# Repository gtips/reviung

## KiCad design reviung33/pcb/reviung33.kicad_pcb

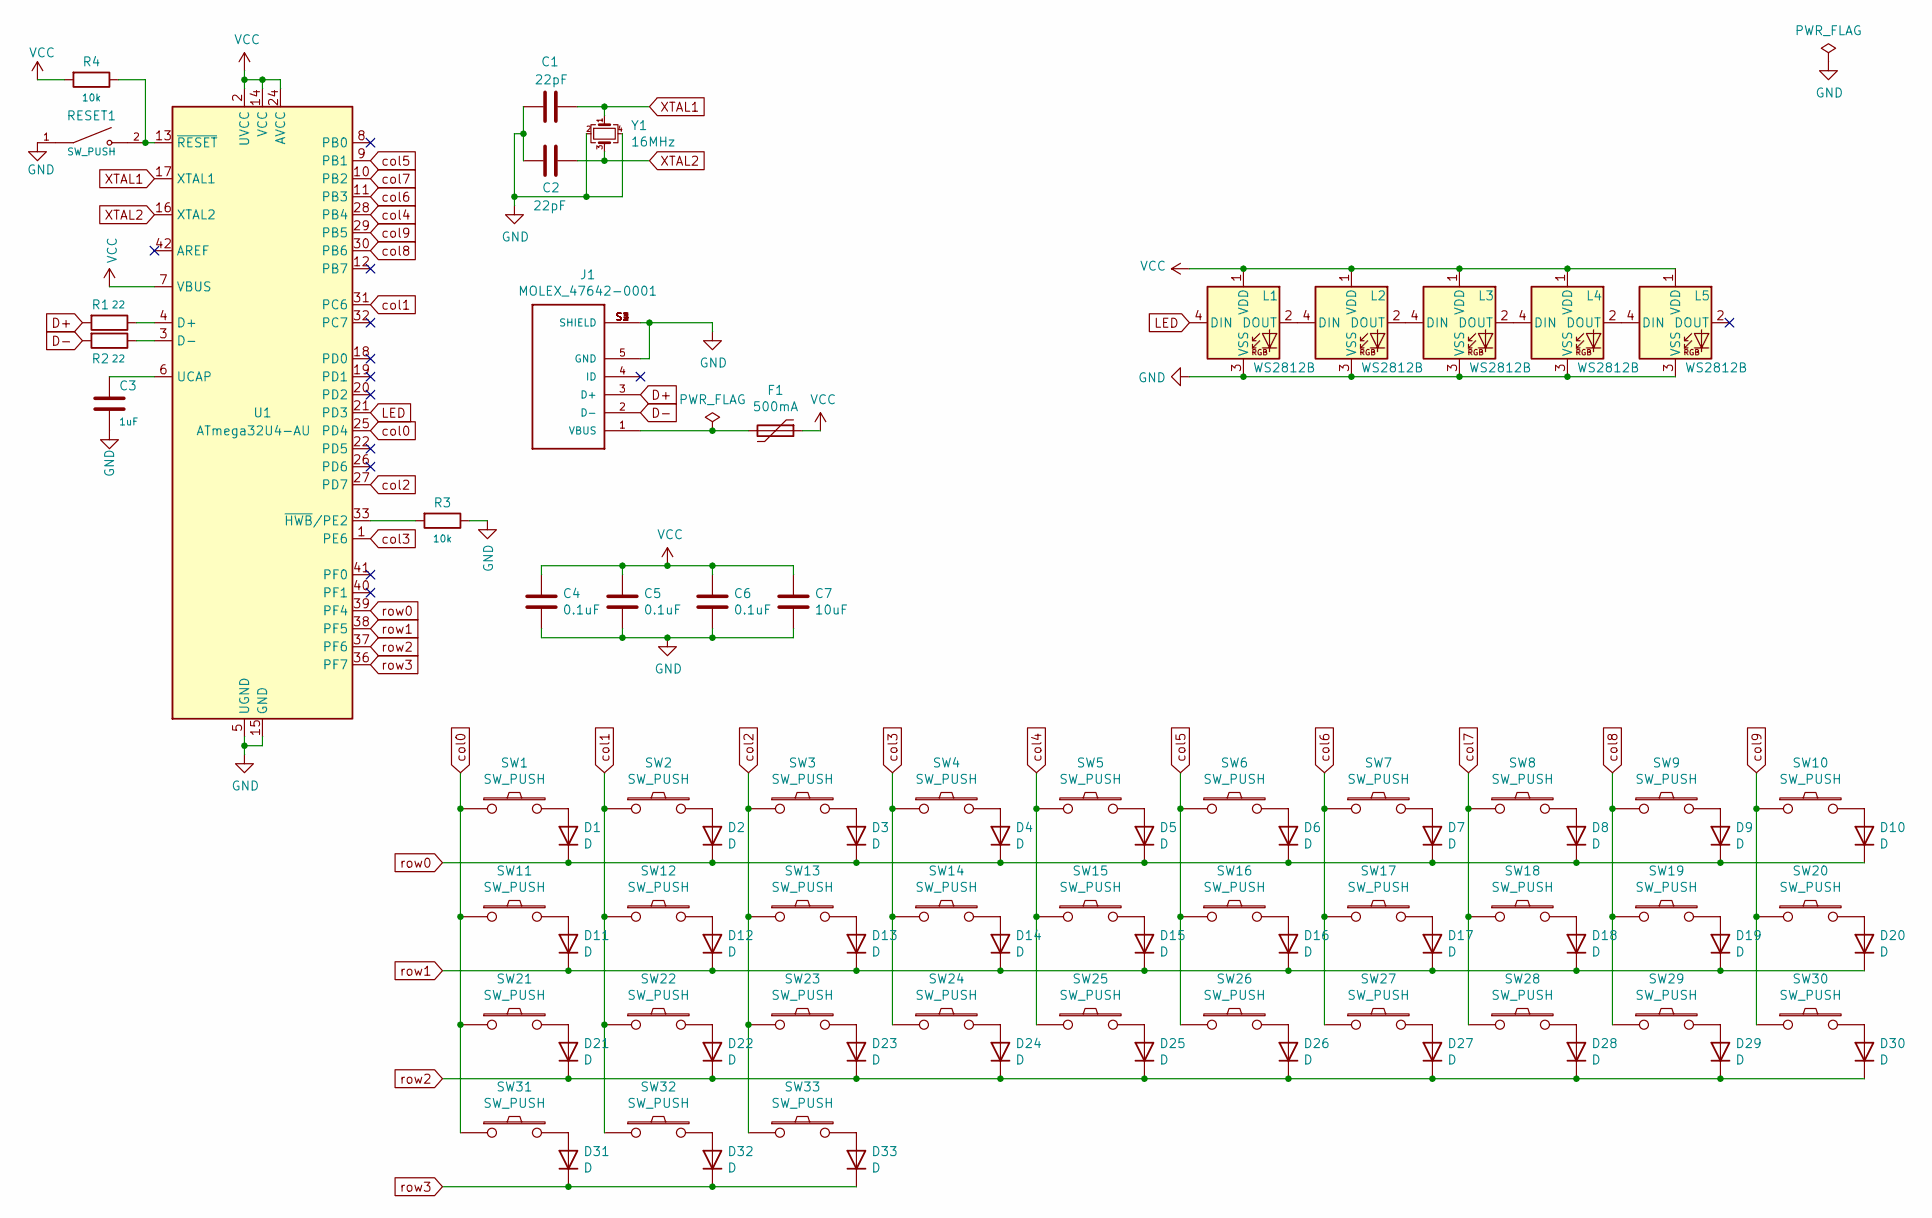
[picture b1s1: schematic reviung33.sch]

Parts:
C1, C2: 22pF; C_1206_3216Metric_Pad1.42x1.75mm_HandSolder
C3: 1uF; C_1206_3216Metric_Pad1.42x1.75mm_HandSolder
C4, C5, C6: 0.1uF; C_1206_3216Metric_Pad1.42x1.75mm_HandSolder
C7: 10uF; C_1206_3216Metric_Pad1.42x1.75mm_HandSolder
D1, D2, D3, D4, D5, D6, D7, D8, D9, D10, D11, D12, D13, D14, D15, D16, D17, D18, D19, D20, D21, D22, D23, D24, D25, D26, D27, D28, D29, D30, D31, D32, D33: D; D3_SMD_1side
F1: 500mA; Fuse_0805_2012Metric_Pad1.15x1.40mm_HandSolder
J1: MOLEX_47642-0001; MOLEX_47642-0001_HandSoldering_cuts
L1, L2, L3, L4, L5: WS2812B; LED_WS2812B_PLCC4_5.0x5.0mm_P3.2mm
R1, R2: 22; R_1206_3216Metric_Pad1.42x1.75mm_HandSolder
R3, R4: 10k; R_1206_3216Metric_Pad1.42x1.75mm_HandSolder
RESET1: SW_PUSH; SW_SPST_B3U-1000P
SW1, SW2, SW3, SW4, SW5, SW6, SW7, SW8, SW9, SW10, SW11, SW12, SW13, SW14, SW15, SW16, SW17, SW18, SW19, SW20, SW21, SW22, SW23, SW24, SW25, SW26, SW27, SW28, SW29, SW30, SW31, SW33: SW_PUSH; MXOnly-1U-Hotswap
SW32: SW_PUSH; MXOnly-6.25U-Hotswap-ReversedStabilizers
U1: ATmega32U4-AU; TQFP-44_10x10mm_P0.8mm
Y1: 16MHz; Crystal_SMD_3225-4Pin_3.2x2.5mm_HandSoldering

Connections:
D+: J1.3 (D+), R1.2
D-: J1.2 (D-), R2.2
GND: C1.1, C2.2, C3.2, C4.2, C5.2, C6.2, C7.2, J1.5 (GND), J1.S1 (SHIELD), J1.S2 (SHIELD), J1.S3 (SHIELD), J1.S4 (SHIELD), L1.3 (VSS), L2.3 (VSS), L3.3 (VSS), L4.3 (VSS), L5.3 (VSS), R3.1, RESET1.1, U1.5 (UGND), U1.15 (GND), U1.23 (GND), U1.35 (GND), U1.43 (GND), Y1.2, Y1.4; also elsewhere on the board
LED: L1.4 (DIN), U1.21 (PD3)
unnamed: C3.1, U1.6 (UCAP)
unnamed: D1.2 (A), SW1.2
unnamed: D2.2 (A), SW2.2
unnamed: D3.2 (A), SW3.2
unnamed: D4.2 (A), SW4.2
unnamed: D5.2 (A), SW5.2
unnamed: D6.2 (A), SW6.2
unnamed: D7.2 (A), SW7.2
unnamed: D8.2 (A), SW8.2
unnamed: D9.2 (A), SW9.2
unnamed: D10.2 (A), SW10.2
unnamed: D11.2 (A), SW11.2
unnamed: D12.2 (A), SW12.2
unnamed: D13.2 (A), SW13.2
unnamed: D14.2 (A), SW14.2
unnamed: D15.2 (A), SW15.2
unnamed: D16.2 (A), SW16.2
unnamed: D17.2 (A), SW17.2
unnamed: D18.2 (A), SW18.2
unnamed: D19.2 (A), SW19.2
unnamed: D20.2 (A), SW20.2
unnamed: D21.2 (A), SW21.2
unnamed: D22.2 (A), SW22.2
unnamed: D23.2 (A), SW23.2
unnamed: D24.2 (A), SW24.2
unnamed: D25.2 (A), SW25.2
unnamed: D26.2 (A), SW26.2
unnamed: D27.2 (A), SW27.2
unnamed: D28.2 (A), SW28.2
unnamed: D29.2 (A), SW29.2
unnamed: D30.2 (A), SW30.2
unnamed: D31.2 (A), SW31.2
unnamed: D32.2 (A), SW32.2
unnamed: D33.2 (A), SW33.2
unnamed: F1.2, J1.1 (VBUS)
unnamed: L1.2 (DOUT), L2.4 (DIN)
unnamed: L2.2 (DOUT), L3.4 (DIN)
unnamed: L3.2 (DOUT), L4.4 (DIN)
unnamed: L4.2 (DOUT), L5.4 (DIN)
unnamed: R1.1, U1.4 (D+)
unnamed: R2.1, U1.3 (D-)
unnamed: R3.2, U1.33 (~HWB~/PE2)
unnamed 46: R4.1, RESET1.2, U1.13 (~RESET); also elsewhere on the board
VCC: C4.1, C5.1, C6.1, C7.1, F1.1, L1.1 (VDD), L2.1 (VDD), L3.1 (VDD), L4.1 (VDD), L5.1 (VDD), R4.2, U1.2 (UVCC), U1.7 (VBUS), U1.14 (VCC), U1.24 (AVCC), U1.34 (VCC), U1.44 (AVCC)
XTAL1: C1.2, U1.17 (XTAL1), Y1.1
XTAL2: C2.1, U1.16 (XTAL2), Y1.3
col0: SW1.1, SW11.1, SW21.1, SW31.1, U1.25 (PD4)
col1: SW2.1, SW12.1, SW22.1, SW32.1, U1.31 (PC6)
col2: SW3.1, SW13.1, SW23.1, SW33.1, U1.27 (PD7)
col3: SW4.1, SW14.1, SW24.1, U1.1 (PE6)
col4: SW5.1, SW15.1, SW25.1, U1.28 (PB4)
col5: SW6.1, SW16.1, SW26.1, U1.9 (PB1)
col6: SW7.1, SW17.1, SW27.1, U1.11 (PB3)
col7: SW8.1, SW18.1, SW28.1, U1.10 (PB2)
col8: SW9.1, SW19.1, SW29.1, U1.30 (PB6)
col9: SW10.1, SW20.1, SW30.1, U1.29 (PB5)
row0: D1.1 (K), D2.1 (K), D3.1 (K), D4.1 (K), D5.1 (K), D6.1 (K), D7.1 (K), D8.1 (K), D9.1 (K), D10.1 (K), U1.39 (PF4)
row1: D11.1 (K), D12.1 (K), D13.1 (K), D14.1 (K), D15.1 (K), D16.1 (K), D17.1 (K), D18.1 (K), D19.1 (K), D20.1 (K), U1.38 (PF5)
row2: D21.1 (K), D22.1 (K), D23.1 (K), D24.1 (K), D25.1 (K), D26.1 (K), D27.1 (K), D28.1 (K), D29.1 (K), D30.1 (K), U1.37 (PF6)
row3: D31.1 (K), D32.1 (K), D33.1 (K), U1.36 (PF7)

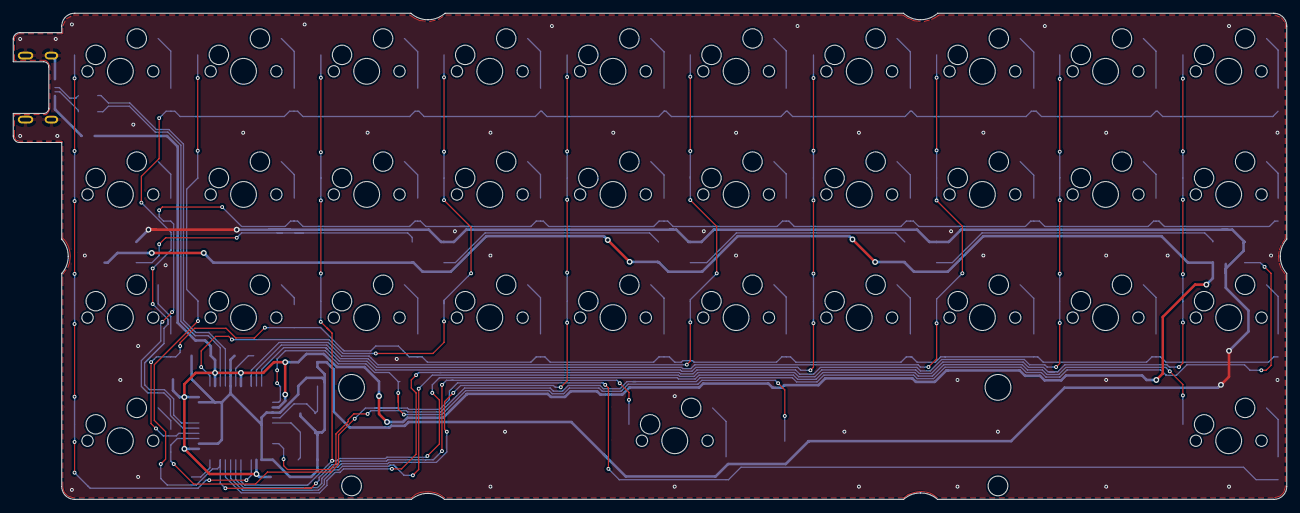
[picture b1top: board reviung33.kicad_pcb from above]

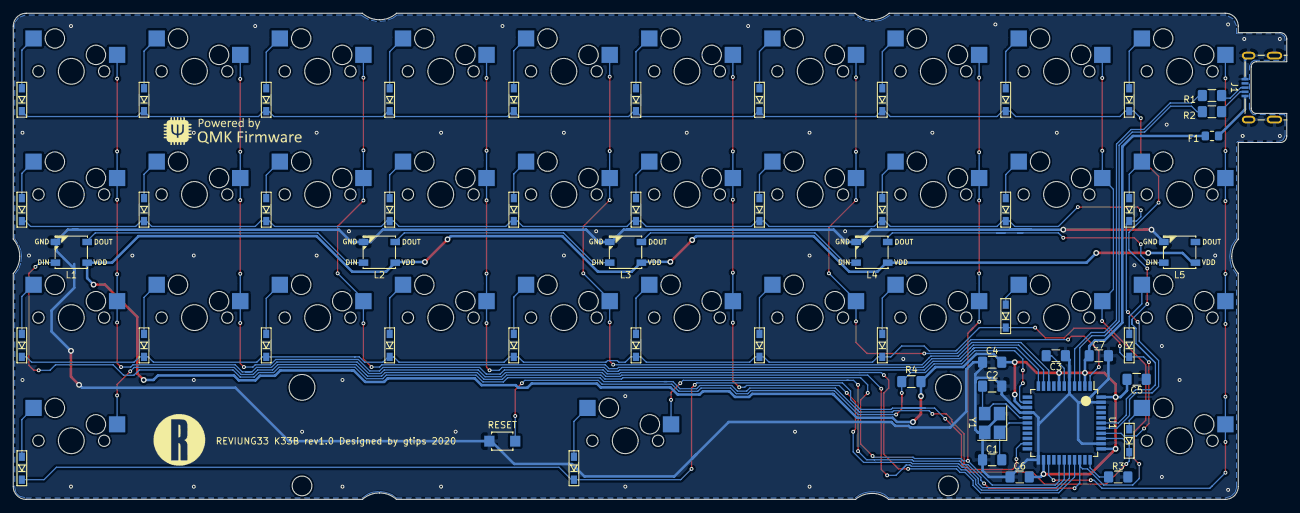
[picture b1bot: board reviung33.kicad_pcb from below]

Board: 2 copper layers, 197.0 x 75.2 mm, 87 parts (54 on the bottom side), 64 nets.

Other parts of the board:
RESET: SW_PUSH; SW_SPST_B3U-1000P

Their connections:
GND: RESET.1; also elsewhere on the board
unnamed 46: RESET.2; also elsewhere on the board
